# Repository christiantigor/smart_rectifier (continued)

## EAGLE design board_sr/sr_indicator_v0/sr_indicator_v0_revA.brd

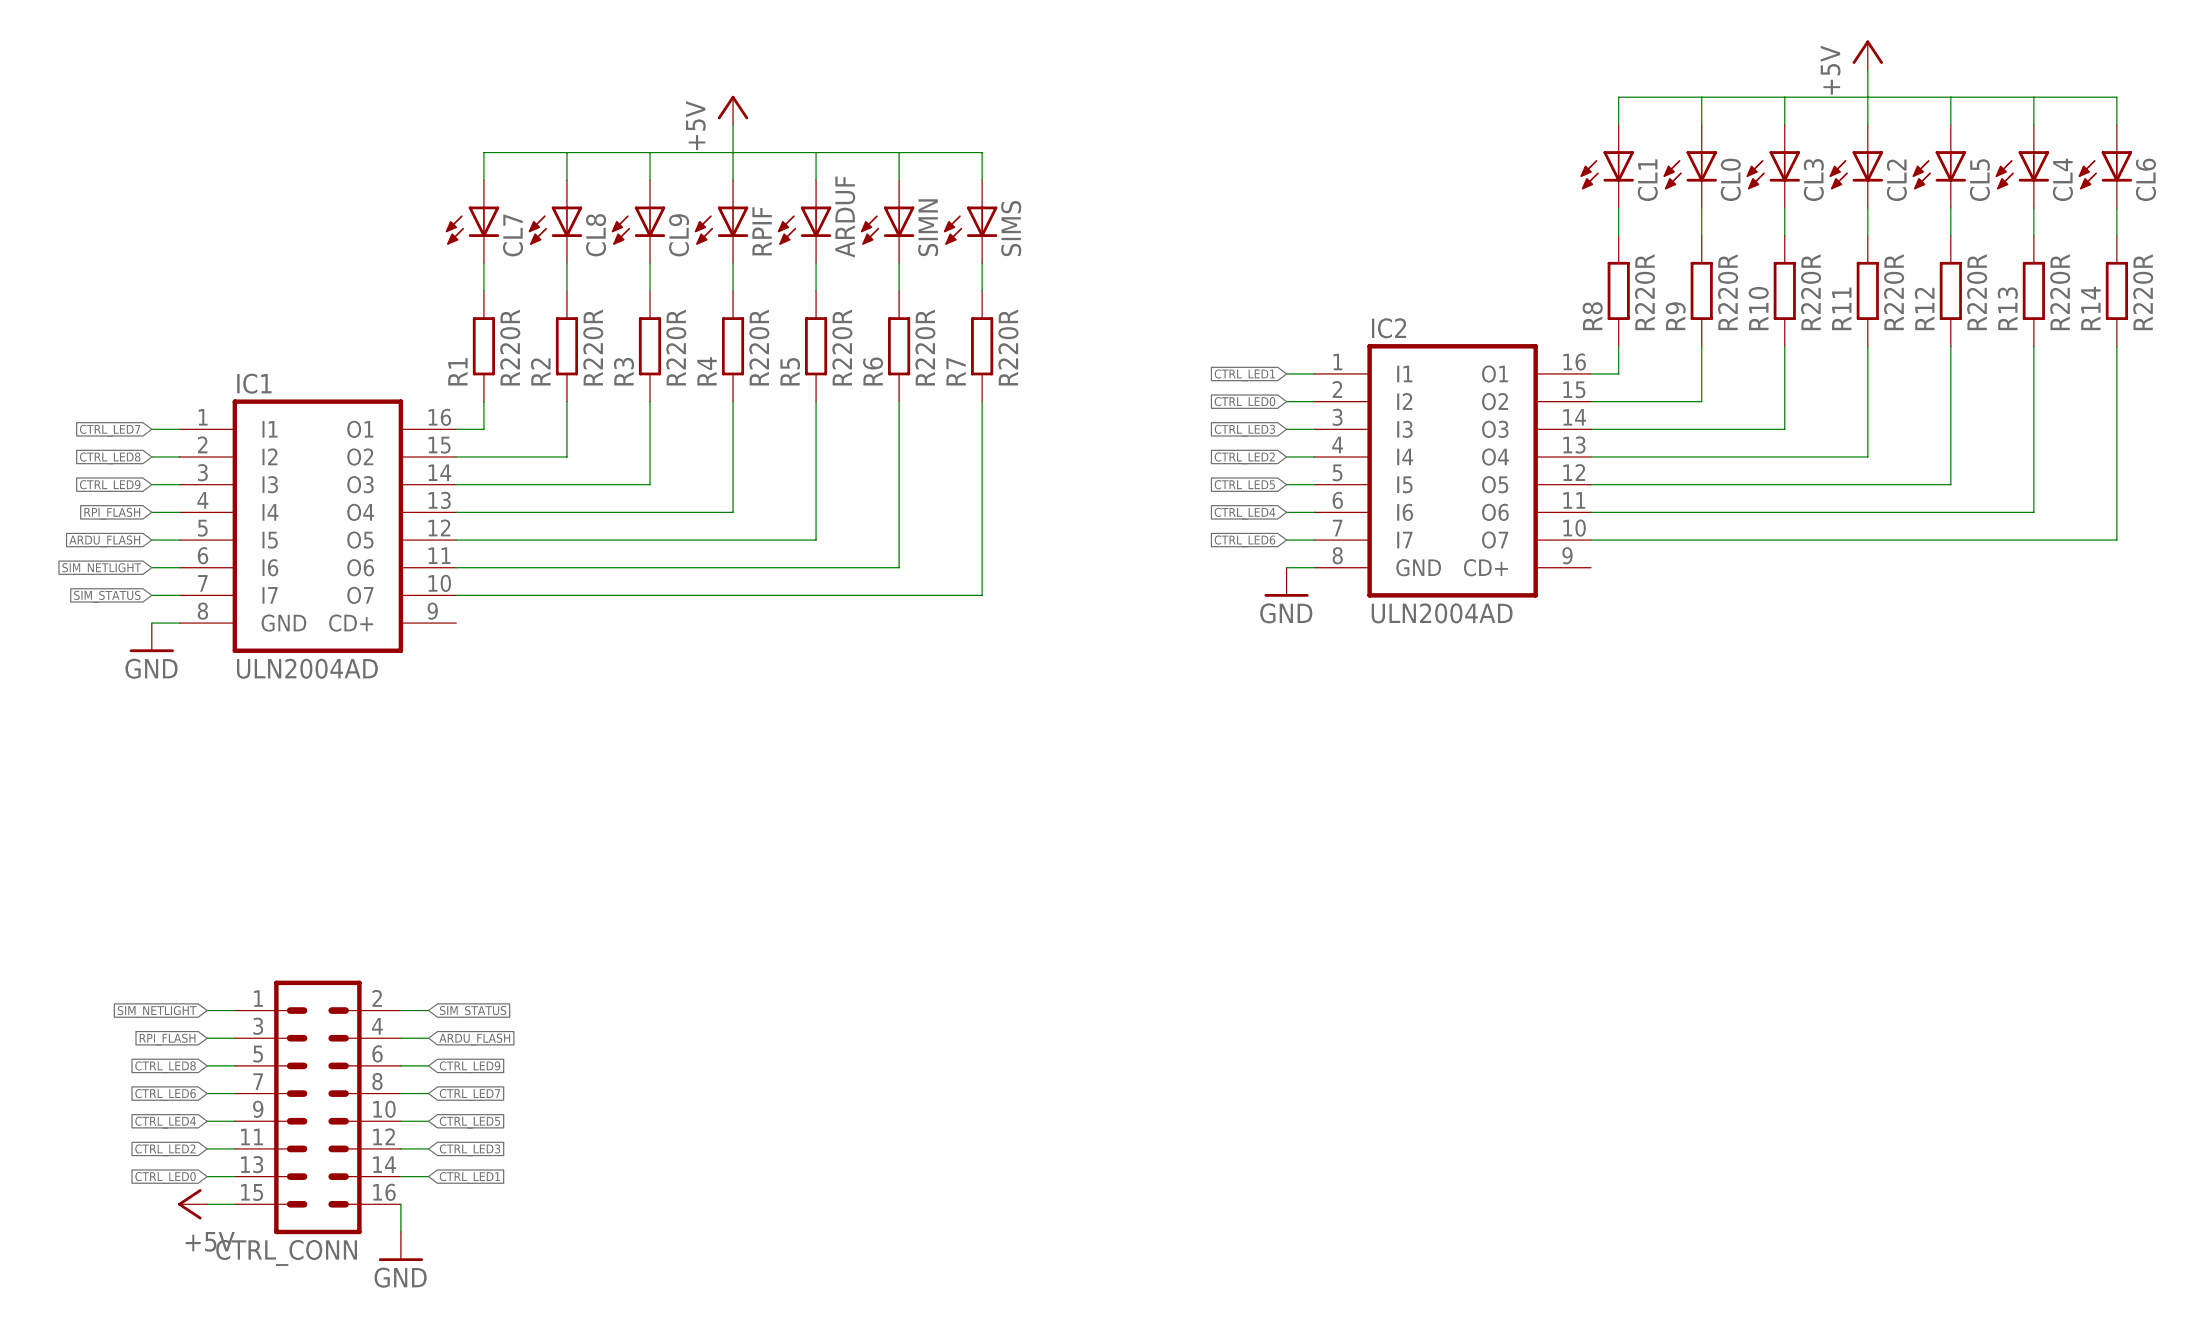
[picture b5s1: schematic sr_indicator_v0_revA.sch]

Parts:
ARDUF: LED3MM
CL0, CL1, CL2, CL3, CL4, CL5, CL6, CL7, CL8, CL9: LED3MM
CTRL_CONN: MA08-2
IC1, IC2: ULN2004AD; SO16
R1, R2, R3, R4, R5, R6, R7, R8, R9, R10, R11, R12, R13, R14: R220R; M0805
RPIF: LED3MM
SIMN: LED3MM
SIMS: LED3MM

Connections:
+5V: ARDUF.A, CL0.A, CL1.A, CL2.A, CL3.A, CL4.A, CL5.A, CL6.A, CL7.A, CL8.A, CL9.A, CTRL_CONN.15, RPIF.A, SIMN.A, SIMS.A
ARDU_FLASH: CTRL_CONN.4, IC1.5 (I5)
CTRL_LED0: CTRL_CONN.13, IC2.2 (I2)
CTRL_LED1: CTRL_CONN.14, IC2.1 (I1)
CTRL_LED2: CTRL_CONN.11, IC2.4 (I4)
CTRL_LED3: CTRL_CONN.12, IC2.3 (I3)
CTRL_LED4: CTRL_CONN.9, IC2.6 (I6)
CTRL_LED5: CTRL_CONN.10, IC2.5 (I5)
CTRL_LED6: CTRL_CONN.7, IC2.7 (I7)
CTRL_LED7: CTRL_CONN.8, IC1.1 (I1)
CTRL_LED8: CTRL_CONN.5, IC1.2 (I2)
CTRL_LED9: CTRL_CONN.6, IC1.3 (I3)
GND: CTRL_CONN.16, IC1.8 (GND), IC2.8 (GND)
unnamed: IC1.16 (O1), R1.1
unnamed: IC1.15 (O2), R2.1
unnamed: IC1.14 (O3), R3.1
unnamed: IC1.13 (O4), R4.1
unnamed: IC1.12 (O5), R5.1
unnamed: IC1.11 (O6), R6.1
unnamed: IC1.10 (O7), R7.1
unnamed: CL7.K (C), R1.2
unnamed: CL8.K (C), R2.2
unnamed: CL9.K (C), R3.2
unnamed: R4.2, RPIF.K (C)
unnamed: ARDUF.K (C), R5.2
unnamed: R6.2, SIMN.K (C)
unnamed: R7.2, SIMS.K (C)
unnamed: IC2.16 (O1), R8.1
unnamed: IC2.15 (O2), R9.1
unnamed: IC2.14 (O3), R10.1
unnamed: IC2.13 (O4), R11.1
unnamed: IC2.12 (O5), R12.1
unnamed: IC2.11 (O6), R13.1
unnamed: IC2.10 (O7), R14.1
unnamed: CL1.K (C), R8.2
unnamed: CL0.K (C), R9.2
unnamed: CL3.K (C), R10.2
unnamed: CL2.K (C), R11.2
unnamed: CL5.K (C), R12.2
unnamed: CL4.K (C), R13.2
unnamed: CL6.K (C), R14.2
RPI_FLASH: CTRL_CONN.3, IC1.4 (I4)
SIM_NETLIGHT: CTRL_CONN.1, IC1.6 (I6)
SIM_STATUS: CTRL_CONN.2, IC1.7 (I7)

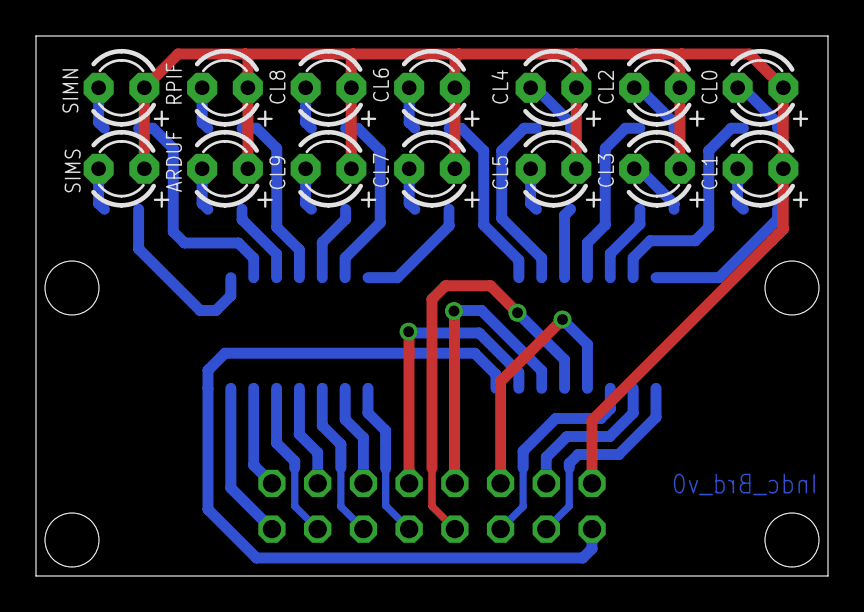
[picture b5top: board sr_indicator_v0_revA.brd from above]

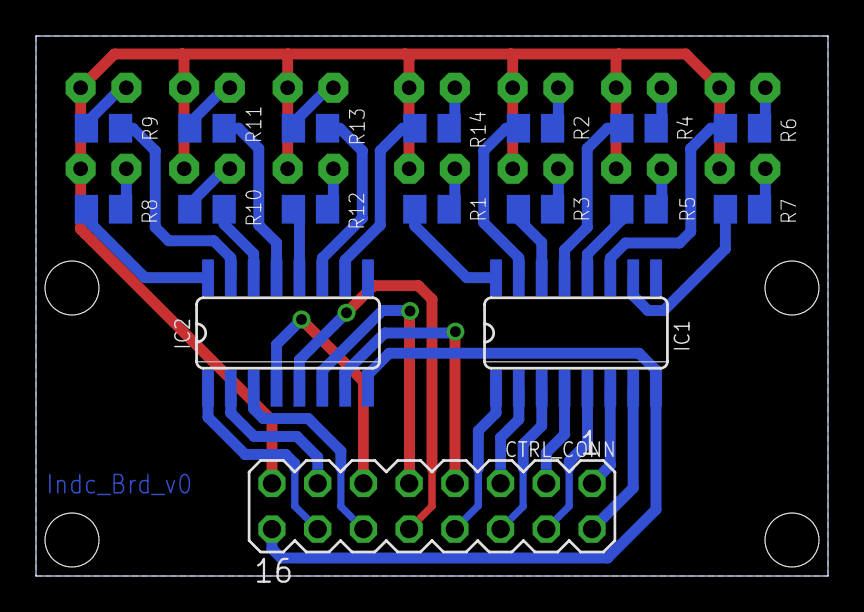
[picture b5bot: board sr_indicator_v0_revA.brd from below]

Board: 2 copper layers, 44.0 x 30.0 mm, 31 parts (17 on the bottom side), 44 nets.

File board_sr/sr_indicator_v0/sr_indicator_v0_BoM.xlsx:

Reference | Part Number | Description | Value | Amount
ARDUF, CL0, CL1, CL2, CL3, CL4, CL5, CL6, CL7, CL8, CL9, RPIF, SIMN, SIMS | LED3MM | LED |  | 14
CTRL_CONN | MA08-2 | Male Pin Header |  | 1
R1, R2, R3, R4, R5, R6, R7, R8, R9, R10, R11, R12, R13, R14 | R-EU_M0805 | R0805 | R220R | 14
IC1, IC2 | ULN2004AD | Driver Array | ULN2004AD | 2

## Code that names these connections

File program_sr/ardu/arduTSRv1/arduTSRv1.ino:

#include "DHT.h"

#define DHTPIN  10
#define DHTTYPE DHT11

DHT dht(DHTPIN, DHTTYPE);

//sensor pin
byte SENSOR_VAC     = 3;
byte SENSOR_VBAT    = 1;
byte SENSOR_IBAT    = 0;
byte SENSOR_ILOAD   = 2;
byte SENSOR_48V_A   = 5;
byte SENSOR_48V_B   = 4;
byte SENSOR_24V     = 7;
byte SENSOR_SPLY    = 6;

//sensor value
int   adcVal        = 0;
int   maxAdcVal     = 0;
long  sumAdcVal     = 0;
long  numReading    = 0;
int   numSamples    = 200;
float valVAC        = 0.0;
float valVBat       = 0.0;
float valIBat       = 0.0;
float valILoad      = 0.0;
float val48V_A      = 0.0;
float val48V_B      = 0.0;
float val24V        = 0.0;
float val6V5        = 0.0;
float val12V        = 0.0;
float val13V5       = 0.0;
float val19V5       = 0.0;
float valTemp       = 0.0;

//sensor calibration
float calbVAC       = 0.4610389610;
float calbVBat      = 0.2334090909;
float calbIBat      = 0.073982;
float calbILoad     = 0.073982;
float calb48V_A     = 0.0536163522;
float calb48V_B     = 0.0537605042;
float calb24V       = 0.0292653673;
float calb16V5      = 0.0097848664;
float calb12V       = 0.0144177671;
float calb13V5      = 0.0144551282;
float calb19V5      = 0.0293917274;

//control pin
byte SEL_SENSOR_1   = 11;
byte SEL_SENSOR_2   = 12;
byte SEL_SENSOR_3   = 13;

//sensor data to send
char    charData[8];
String  strJSON;
String  strData;

int     supplyVoltage;
boolean zeroCross = false;
unsigned long start;

void setup(){
  Serial.begin(57600);
  
  //begin DHT11
  dht.begin();
  delay(2000);
  
  //set sensor pin as input
  
  //set control pin as output
  pinMode(SEL_SENSOR_1, OUTPUT);
  pinMode(SEL_SENSOR_2, OUTPUT);
  pinMode(SEL_SENSOR_3, OUTPUT);
  
  //set control pin default
  digitalWrite(SEL_SENSOR_1, LOW);
  digitalWrite(SEL_SENSOR_2, LOW);
  digitalWrite(SEL_SENSOR_3, LOW);

  //discarding first readings
  //for(int i=0; i<numSamples; i++) {
  //  analogRead(SENSOR_VAC);  
  //}
}

void loop(){
  //read sensor value
  
  while(true){
    //VAC
    start = millis();
    zeroCross = false;
    while(!zeroCross) {
      adcVal = analogRead(SENSOR_VAC);
      if(adcVal < 100.0) {
        Serial.print("\n");
        zeroCross = true;  
      } 
      if((millis()-start)>2000) zeroCross = true;  
    }

    //find max ADC val for VAC for certain duration
    //the max ADC value indicate the real VAC voltage
    //we choose this method instead of RMS to make it sense surge voltage
    start = millis();
    maxAdcVal = 0;
    while(true){
      adcVal = analogRead(SENSOR_VAC);
      if(adcVal > maxAdcVal) {
        maxAdcVal = adcVal;  
      }
      delay(1);
      if((millis()-start)>500) break;
    }

    //handle case when there is no VAC, but ADC is not zero
    if(maxAdcVal > 100.0) {
      valVAC = maxAdcVal * calbVAC;
    } else {
      valVAC = 0.0;  
    }
    //Serial.println(valVAC);
	
    //VBat
    sumAdcVal = 0;
    for(int i=0; i<numSamples; i++) {
    	sumAdcVal += analogRead(SENSOR_VBAT);  
    }
    adcVal = int(sumAdcVal/numSamples);
    valVBat = adcVal * calbVBat;
    
    //IBat
    sumAdcVal = 0;
    for(int i=0; i<numSamples; i++) {
    	sumAdcVal += analogRead(SENSOR_IBAT);  
    }
    adcVal = int(sumAdcVal/numSamples);
    valIBat = (adcVal-511.0) * calbIBat;
    //res_adc(V/step) / res_acs(V/A) = A/step
    //5/1024          / 0.066
    
    //ILoad
    sumAdcVal = 0;
    for(int i=0; i<numSamples; i++) {
    	sumAdcVal += analogRead(SENSOR_ILOAD);  
    }
    adcVal = int(sumAdcVal/numSamples);
    valILoad = (adcVal-511.0) * calbILoad;
    
    //48V_A
    sumAdcVal = 0;
    for(int i=0; i<numSamples; i++) {
    	sumAdcVal += analogRead(SENSOR_48V_A);  
    }
    adcVal = int(sumAdcVal/numSamples);
    val48V_A = adcVal * calb48V_A;
    
    //48V_B
    sumAdcVal = 0;
    for(int i=0; i<numSamples; i++) {
    	sumAdcVal += analogRead(SENSOR_48V_B);  
    }
    adcVal = int(sumAdcVal/numSamples);
    val48V_B = adcVal * calb48V_B;
    
    //24V
    sumAdcVal = 0;
    for(int i=0; i<numSamples; i++) {
    	sumAdcVal += analogRead(SENSOR_24V);  
    }
    adcVal = int(sumAdcVal/numSamples);
    val24V = adcVal * calb24V;
    
    //SEL_SENSOR_1 = 0; SEL_SENSOR_2 = X; SEL_SENSOR_3 = 0 -> 6V5
    digitalWrite(SEL_SENSOR_1, LOW);
    digitalWrite(SEL_SENSOR_3, LOW);
    delay(10);
    sumAdcVal = 0;
    for(int i=0; i<numSamples; i++) {
    	sumAdcVal += analogRead(SENSOR_SPLY);  
    }
    adcVal = int(sumAdcVal/numSamples);
    val6V5 = adcVal * calb16V5;
    
    //SEL_SENSOR_1 = 0; SEL_SENSOR_2 = X; SEL_SENSOR_3 = 1 -> 12V
    digitalWrite(SEL_SENSOR_1, LOW);
    digitalWrite(SEL_SENSOR_3, HIGH);
    delay(10);
    sumAdcVal = 0;
    for(int i=0; i<numSamples; i++) {
    	sumAdcVal += analogRead(SENSOR_SPLY);  
    }
    adcVal = int(sumAdcVal/numSamples);
    val12V = adcVal * calb12V;
    
    //SEL_SENSOR_1 = 1; SEL_SENSOR_2 = 0; SEL_SENSOR_3 = X -> 13V5
    digitalWrite(SEL_SENSOR_1, HIGH);
    digitalWrite(SEL_SENSOR_2, LOW);
    delay(10);
    sumAdcVal = 0;
    for(int i=0; i<numSamples; i++) {
    	sumAdcVal += analogRead(SENSOR_SPLY);  
    }
    adcVal = int(sumAdcVal/numSamples);
    val13V5 = adcVal * calb13V5;
    
    //SEL_SENSOR_1 = 1; SEL_SENSOR_2 = 1; SEL_SENSOR_3 = X -> 19V5
    digitalWrite(SEL_SENSOR_1, HIGH);
    digitalWrite(SEL_SENSOR_2, HIGH);
    delay(10);
    sumAdcVal = 0;
    for(int i=0; i<numSamples; i++) {
    	sumAdcVal += analogRead(SENSOR_SPLY);  
    }
    adcVal = int(sumAdcVal/numSamples);
    val19V5 = adcVal * calb19V5;
    
    //temperature sensor
    valTemp = dht.readTemperature();
    if(isnan(valTemp)) {
    	valTemp = 0.0;
    }
    
    //construct data
    strJSON = "{\"VAC\":\"";
    dtostrf(valVAC,4,2,charData);
    strData = String(charData);
    strJSON += strData;
    
    strJSON += "\",\"VBat\":\"";
    dtostrf(valVBat,4,2,charData);
    strData = String(charData);
    strJSON += strData;
    
    strJSON += "\",\"IBat\":\"";
    dtostrf(valIBat,4,2,charData);
    strData = String(charData);
    strJSON += strData;
    
    strJSON += "\",\"ILoad\":\"";
    dtostrf(valILoad,4,2,charData);
    strData = String(charData);
    strJSON += strData;
    
    strJSON += "\",\"6V5\":\"";
    dtostrf(val6V5,4,2,charData);
    strData = String(charData);
    strJSON += strData;
    
    strJSON += "\",\"12V\":\"";
    dtostrf(val12V,4,2,charData);
    strData = String(charData);
    strJSON += strData;
    
    strJSON += "\",\"13V5\":\"";
    dtostrf(val13V5,4,2,charData);
    strData = String(charData);
    strJSON += strData;
    
    strJSON += "\",\"19V5\":\"";
    dtostrf(val19V5,4,2,charData);
    strData = String(charData);
    strJSON += strData;
    
    strJSON += "\",\"24V\":\"";
    dtostrf(val24V,4,2,charData);
    strData = String(charData);
    strJSON += strData;
    
    strJSON += "\",\"48V_A\":\"";
    dtostrf(val48V_A,4,2,charData);
    strData = String(charData);
    strJSON += strData;
    
    strJSON += "\",\"48V_B\":\"";
    dtostrf(val48V_B,4,2,charData);
    strData = String(charData);
    strJSON += strData;
    
    strJSON += "\",\"Temp\":\"";
    dtostrf(valTemp,4,2,charData);
    strData = String(charData);
    strJSON += strData;
    
    strJSON += "\"}";
    
    //send data via serial
    Serial.println(strJSON);
    
    //some delay
    delay(1000);
  }
}

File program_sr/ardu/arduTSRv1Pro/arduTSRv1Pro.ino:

//Arduino code for PCB production

#include "DHT.h"
#define DHTPIN  10
#define DHTTYPE DHT11

DHT dht(DHTPIN, DHTTYPE);

//sensor pin
byte SENSOR_VAC       = 3;
byte SENSOR_VPS       = 2;
byte SENSOR_IBAT      = 1;
byte SENSOR_ILOAD     = 0;
byte SENSOR_SPLY_A    = 6;  //PCB production use Arduino with swapped pin between A6 and A7
byte SENSOR_SPLY_B    = 7;  //PCB production use Arduino with swapped pin between A6 and A7

//sensor value
int   adcVal        = 0;
int   maxAdcVal     = 0;
long  sumAdcVal     = 0;
long  numReading    = 0;
int   numSamples    = 200;
float valVAC        = 0.0;
float valVPwrSply   = 0.0;
float valVBat       = 0.0;
float valIBat       = 0.0;
float valILoad      = 0.0;
float val48V_A      = 0.0;
float val48V_B      = 0.0;
float val24V        = 0.0;
float val6V5        = 0.0;
float val12V        = 0.0;
float val13V5       = 0.0;
float val19V5       = 0.0;
float valTemp       = 0.0;

//sensor calibration
float calbVAC       = 0.7138157894;
float calbVPS       = 0.2334090909;
float calbVBat      = 0.2334090909;
float calbIBat      = 0.073982;
float calbILoad     = 0.073982;
float calb48V_A     = 0.0536163522;
float calb48V_B     = 0.0537605042;
float calb24V       = 0.0292653673;
float calb6V5       = 0.0097848664;
float calb12V       = 0.0144177671;
float calb13V5      = 0.0144551282;
float calb19V5      = 0.0293917274;

//control pin
byte SEL_SENSOR_1   = 11;
byte SEL_SENSOR_2   = 12;

//sensor data to send
char    charData[8];
String  strJSON;
String  strData;

int     supplyVoltage;
boolean zeroCross = false;
unsigned long start;

void setup(){
  Serial.begin(57600);
  
  //begin DHT11
  dht.begin();
  delay(2000);
  
  //set sensor pin as input
  
  //set control pin as output
  pinMode(SEL_SENSOR_1, OUTPUT);
  pinMode(SEL_SENSOR_2, OUTPUT);
  
  //set control pin default
  digitalWrite(SEL_SENSOR_1, LOW);
  digitalWrite(SEL_SENSOR_2, LOW);

  //discarding first readings
  //for(int i=0; i<numSamples; i++) {
  //  analogRead(SENSOR_VAC);  
  //}
}

void loop(){
  //read sensor value
  
  while(true){
    //VAC
    start = millis();
    zeroCross = false;
    while(!zeroCross) {
      adcVal = analogRead(SENSOR_VAC);
      if(adcVal < 100.0) {
        Serial.print("\n");
        zeroCross = true;  
      } 
      if((millis()-start)>2000) zeroCross = true;  
    }

    //find max ADC val for VAC for certain duration
    //the max ADC value indicate the real VAC voltage
    //we choose this method instead of RMS to make it sense surge voltage
    start = millis();
    maxAdcVal = 0;
    while(true){
      adcVal = analogRead(SENSOR_VAC);
      if(adcVal > maxAdcVal) {
        maxAdcVal = adcVal;  
      }
      delay(1);
      if((millis()-start)>500) break;
    }

    //handle case when there is no VAC, but ADC is not zero
    if(maxAdcVal > 100.0) {
      valVAC = maxAdcVal * calbVAC;
    } else {
      valVAC = 0.0;  
    }
    //Serial.println(valVAC);
	
    //VPS
    sumAdcVal = 0;
    for(int i=0; i<numSamples; i++) {
      sumAdcVal += analogRead(SENSOR_VPS);  
    }
    adcVal = int(sumAdcVal/numSamples);
    valVPwrSply = adcVal * calbVPS;

    //IBat
    sumAdcVal = 0;
    for(int i=0; i<numSamples; i++) {
      sumAdcVal += analogRead(SENSOR_IBAT);  
    }
    adcVal = int(sumAdcVal/numSamples);
    valIBat = (adcVal-511.0) * calbIBat;
    //res_adc(V/step) / res_acs(V/A) = A/step
    //5/1024          / 0.066
    
    //ILoad
    sumAdcVal = 0;
    for(int i=0; i<numSamples; i++) {
      sumAdcVal += analogRead(SENSOR_ILOAD);  
    }
    adcVal = int(sumAdcVal/numSamples);
    valILoad = (adcVal-511.0) * calbILoad;

    //SENSOR_SPLY_A
    //SEL_SENSOR_1 = 0; SEL_SENSOR_2 = 0; -> 24V
    digitalWrite(SEL_SENSOR_1, LOW);
    digitalWrite(SEL_SENSOR_2, LOW);
    delay(10);
    sumAdcVal = 0;
    for(int i=0; i<numSamples; i++) {
      sumAdcVal += analogRead(SENSOR_SPLY_A);  
    }
    adcVal = int(sumAdcVal/numSamples);
    val24V = adcVal * calb24V;
    
    //SEL_SENSOR_1 = 0; SEL_SENSOR_2 = 1; -> 48V_B
    digitalWrite(SEL_SENSOR_1, LOW);
    digitalWrite(SEL_SENSOR_2, HIGH);
    delay(10);
    sumAdcVal = 0;
    for(int i=0; i<numSamples; i++) {
      sumAdcVal += analogRead(SENSOR_SPLY_A);  
    }
    adcVal = int(sumAdcVal/numSamples);
    val48V_B = adcVal * calb48V_B;
    
    //SEL_SENSOR_1 = 1; SEL_SENSOR_2 = 0; -> 48V_A
    digitalWrite(SEL_SENSOR_1, HIGH);
    digitalWrite(SEL_SENSOR_2, LOW);
    delay(10);
    sumAdcVal = 0;
    for(int i=0; i<numSamples; i++) {
      sumAdcVal += analogRead(SENSOR_SPLY_A);  
    }
    adcVal = int(sumAdcVal/numSamples);
    val48V_A = adcVal * calb48V_A;
    
    //SEL_SENSOR_1 = 1; SEL_SENSOR_2 = 1; -> VBat
    digitalWrite(SEL_SENSOR_1, HIGH);
    digitalWrite(SEL_SENSOR_2, HIGH);
    delay(10);
    sumAdcVal = 0;
    for(int i=0; i<numSamples; i++) {
      sumAdcVal += analogRead(SENSOR_SPLY_A);  
    }
    adcVal = int(sumAdcVal/numSamples);
    valVBat = adcVal * calbVBat;

    //SENSOR_SPLY_B
    //SEL_SENSOR_1 = 0; SEL_SENSOR_2 = 0; -> 6V5
    digitalWrite(SEL_SENSOR_1, LOW);
    digitalWrite(SEL_SENSOR_2, LOW);
    delay(10);
    sumAdcVal = 0;
    for(int i=0; i<numSamples; i++) {
      sumAdcVal += analogRead(SENSOR_SPLY_B);  
    }
    adcVal = int(sumAdcVal/numSamples);
    val6V5 = adcVal * calb6V5;

    //SEL_SENSOR_1 = 0; SEL_SENSOR_2 = 1; -> 12V
    digitalWrite(SEL_SENSOR_1, LOW);
    digitalWrite(SEL_SENSOR_2, HIGH);
    delay(10);
    sumAdcVal = 0;
    for(int i=0; i<numSamples; i++) {
      sumAdcVal += analogRead(SENSOR_SPLY_B);  
    }
    adcVal = int(sumAdcVal/numSamples);
    val12V = adcVal * calb12V;
    
    //SEL_SENSOR_1 = 1; SEL_SENSOR_2 = 0; -> 13V5
    digitalWrite(SEL_SENSOR_1, HIGH);
    digitalWrite(SEL_SENSOR_2, LOW);
    delay(10);
    sumAdcVal = 0;
    for(int i=0; i<numSamples; i++) {
      sumAdcVal += analogRead(SENSOR_SPLY_B);  
    }
    adcVal = int(sumAdcVal/numSamples);
    val13V5 = adcVal * calb13V5;
    
    //SEL_SENSOR_1 = 1; SEL_SENSOR_2 = 1; -> 19V5
    digitalWrite(SEL_SENSOR_1, HIGH);
    digitalWrite(SEL_SENSOR_2, HIGH);
    delay(10);
    sumAdcVal = 0;
    for(int i=0; i<numSamples; i++) {
      sumAdcVal += analogRead(SENSOR_SPLY_B);  
    }
    adcVal = int(sumAdcVal/numSamples);
    val19V5 = adcVal * calb19V5;
    
    //temperature sensor
    valTemp = dht.readTemperature();
    if(isnan(valTemp)) {
    	valTemp = 0.0;
    }
    
    //construct data
    strJSON = "{\"VAC\":\"";
    dtostrf(valVAC,4,2,charData);
    strData = String(charData);
    strJSON += strData;

    strJSON += "\",\"VPS\":\"";
    dtostrf(valVPwrSply,4,2,charData);
    strData = String(charData);
    strJSON += strData;
    
    strJSON += "\",\"VBat\":\"";
    dtostrf(valVBat,4,2,charData);
    strData = String(charData);
    strJSON += strData;
    
    strJSON += "\",\"IBat\":\"";
    dtostrf(valIBat,4,2,charData);
    strData = String(charData);
    strJSON += strData;
    
    strJSON += "\",\"ILoad\":\"";
    dtostrf(valILoad,4,2,charData);
    strData = String(charData);
    strJSON += strData;
    
    strJSON += "\",\"6V5\":\"";
    dtostrf(val6V5,4,2,charData);
    strData = String(charData);
    strJSON += strData;
    
    strJSON += "\",\"12V\":\"";
    dtostrf(val12V,4,2,charData);
    strData = String(charData);
    strJSON += strData;
    
    strJSON += "\",\"13V5\":\"";
    dtostrf(val13V5,4,2,charData);
    strData = String(charData);
    strJSON += strData;
    
    strJSON += "\",\"19V5\":\"";
    dtostrf(val19V5,4,2,charData);
    strData = String(charData);
    strJSON += strData;
    
    strJSON += "\",\"24V\":\"";
    dtostrf(val24V,4,2,charData);
    strData = String(charData);
    strJSON += strData;
    
    strJSON += "\",\"48V_A\":\"";
    dtostrf(val48V_A,4,2,charData);
    strData = String(charData);
    strJSON += strData;
    
    strJSON += "\",\"48V_B\":\"";
    dtostrf(val48V_B,4,2,charData);
    strData = String(charData);
    strJSON += strData;
    
    strJSON += "\",\"Temp\":\"";
    dtostrf(valTemp,4,2,charData);
    strData = String(charData);
    strJSON += strData;
    
    strJSON += "\"}";
    
    //send data via serial
    Serial.println(strJSON);
    
    //some delay
    delay(1000);
  }
}

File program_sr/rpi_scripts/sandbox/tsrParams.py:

#!/usr/bin/python
 
#Columns of srCurrent table
#Used in:
#readSensor.py
cols = ['srVAC','srVPS','srVBat','srIBat','srILoad','sr6V5','sr12V','sr13V5','sr19V5','sr24V','sr48V_A','sr48V_B','srTemp']

#Coefficient sensor values
coefSen = {
    cols[0]:0.4610389610,
    cols[1]:0.2334090909,
    cols[2]:0.2334090909,
    cols[3]:0.073982,
    cols[4]:0.073982,
    cols[5]:0.0536163522,
    cols[6]:0.0537605042,
    cols[7]:0.0292653673,
    cols[8]:0.0097848664,
    cols[9]:0.0144177671,
    cols[10]:0.0144551282,
    cols[11]:0.0293917274
}

#Default sensor values
defSen = {cols[0]:220, cols[1]:56, cols[2]:56, cols[5]:6.5, cols[6]:12, cols[7]:13.5, cols[8]:19.5, cols[9]:24, cols[10]:56, cols[11]:56, cols[12]:25}

#LED pin
ledPin = {'INDC_SPLY_OUTS':16, 'INDC_HEALTH_RED':20, 'INDC_HEALTH_GREEN':26}

#Blinking routine of each LED
leds = ['ledSupplyBlue.py','ledHealthRed.py','ledHealthGreen.py']

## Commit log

2015-09-29 :lollipop: Added .gitattributes & .gitignore files
2015-10-07 Placing Components
2015-10-08 Update schematic
2015-10-19 Update PCB design
2015-10-21 Backup routing pcb
2015-10-22 Finish routing
2015-10-29 Finish Routing PCB ver1 revA
2015-11-05 Add Casing CAD Drawing
2015-11-06 Update casing
2015-11-17 Initial commit of getSensorData
2015-11-18 Update program script on RPi
2015-11-21 Update sensor code to del data from DB after read
2015-11-24 Update arduino code and charging test
    Update adc read by mean of samples; charging with and without BUC load
2015-11-29 Add sticker data and update Ardu and RPi code
    Ardu - add indicator
    RPi - TSR Cloud connect with ETH and GPRS
    RPi - Set max DB size for local backup
2016-04-19 Create sr_controller_v1_revB
2016-06-01 Publish sr_controller_v1_revC
2016-06-01 Update sr_controller_v1_revC
2016-06-22 Add sr_controller_v1_revD
2016-07-26 Backup TSR webserver
2016-08-24 Update Arduino Code
2016-08-25 Create rpi scripts
2016-08-30 Create Arduino code for production board
    Move measurement coefficient from Arduino to RPi
2016-08-30 Update ledFlasher script
2016-08-30 Add resetDevice script
    Device will reset if you press button more than 5 second
2017-06-01 Urgent Update board_sr only
    Commited & Pussed by Maula
